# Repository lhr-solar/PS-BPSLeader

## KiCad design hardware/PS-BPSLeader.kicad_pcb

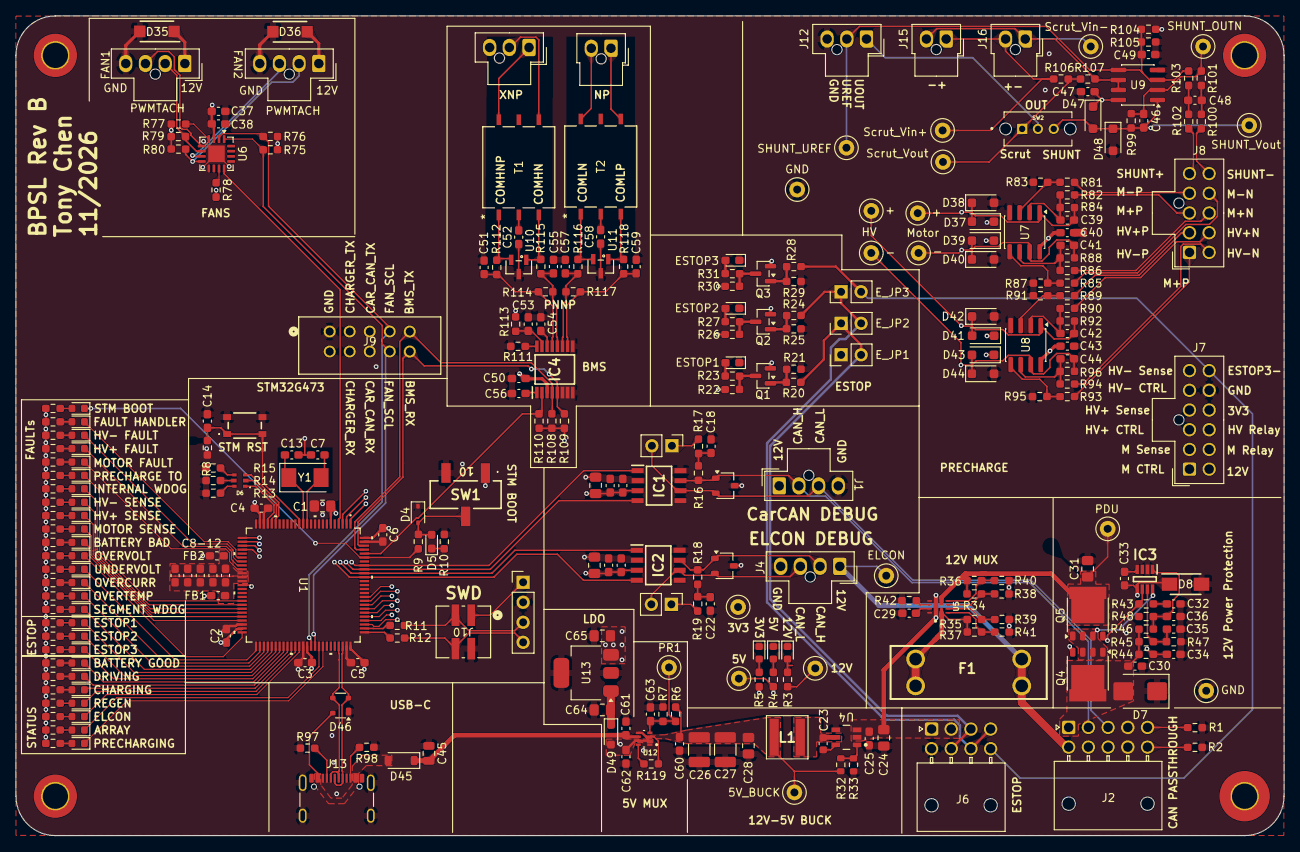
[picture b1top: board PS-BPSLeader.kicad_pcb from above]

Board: 4 copper layers, 160.9 x 104.0 mm, 315 parts (1 on the bottom side), 204 nets.

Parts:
C1, C15, C19, C31, C64, C65: 10u; C_0805_2012Metric_Pad1.18x1.45mm_HandSolder
C2, C3, C4, C5, C6, C8, C9, C12, C14, C16, C17, C18, C20, C21, C22, C30, C35, C36, C40, C43, C47, C50, C53: 0.1u; C_0603_1608Metric_Pad1.08x0.95mm_HandSolder
C7, C13: 26p; C_0603_1608Metric_Pad1.08x0.95mm_HandSolder
C10, C11, C29, C34, C37, C38: 1u; C_0603_1608Metric_Pad1.08x0.95mm_HandSolder
C23: 100n; C_0603_1608Metric
C24: 4.7u; C_0805_2012Metric_Pad1.18x1.45mm_HandSolder
C25, C48, C49: 100n; C_0603_1608Metric_Pad1.08x0.95mm_HandSolder
C26, C27: 22u; C_1210_3225Metric_Pad1.33x2.70mm_HandSolder
C28: 3.3u; C_0805_2012Metric_Pad1.18x1.45mm_HandSolder
C32: 10n; C_0603_1608Metric_Pad1.08x0.95mm_HandSolder
C33: 220n; C_0603_1608Metric_Pad1.08x0.95mm_HandSolder
C39, C41, C42, C44, C46: 1n; C_0603_1608Metric_Pad1.08x0.95mm_HandSolder
C45: 10u; C_0805_2012Metric
C51, C52, C55, C57, C58, C59: 100pF; C_0603_1608Metric_Pad1.08x0.95mm_HandSolder
C54, C56: 0.22u; C_0603_1608Metric_Pad1.08x0.95mm_HandSolder
C60, C61, C62, C63: 0.1uF; C_0603_1608Metric_Pad1.08x0.95mm_HandSolder
D1, D2, D3, D9, D10, D11, D12, D13, D14, D15, D16, D17, D18, D19, D20, D21, D22, D23, D24, D25, D26, D27, D28, D29, D30, D31, D32, D33, D34: LED; LED_0603_1608Metric
D4: TVS; D_SOD-323
D5: LED; LED_0603_1608Metric_Pad1.05x0.95mm_HandSolder
D6: RGB_LED
D7: SMBJ15CA; D_SMB
D8: SMAF4758A; SODFL5026X125N
D35, D36: VSSAF522-M3/H; SODFL5226X100N
D37, D38, D39, D40, D41, D42, D43, D44, D47, D48: TVS; D_SOD-123F
D45: D_Schottky; D_SOD-123
D46: SP0503BAHT; SOT-143
D49: SBA130CH-AU_R1_000A1; D_SOD-323_HandSoldering
E_JP1, E_JP2, E_JP3: Jumper_2_Open; PinHeader_1x02_P2.54mm_Vertical
F1: 5A; Fuse-3557-2
FAN1, FAN2: Conn_01x04; Molex_Nano-Fit_105309-xx04_1x04_P2.50mm_Vertical
FB1, FB2: FerriteBead; L_0603_1608Metric_Pad1.05x0.95mm_HandSolder
H1: MountingHole_Pad; MountingHole_3.2mm_M3_Pad_TopBottom
H2, H3, H4: MountingHole_Pad; MountingHole_3.2mm_M3_ISO14580_Pad_TopBottom
IC1, IC2: TCAN3413DR
IC3: LM74502DDFR
IC4: BQ79600PWRQ1; SOP65P640X120-16N
J1: CAR CAN DEBUG; Molex_Nano-Fit_105309-xx04_1x04_P2.50mm_Vertical
J2: LVC CAN PASSTHROUGH; Molex_Nano-Fit_105314-xx10_2x05_P2.50mm_Horizontal
J3: High Side Conn; Molex_Nano-Fit_105309-xx03_1x03_P2.50mm_Vertical
J4: ELCON CAN DEBUG; Molex_Nano-Fit_105309-xx04_1x04_P2.50mm_Vertical
J5: Low SIde Conn; Molex_Nano-Fit_105309-xx02_1x02_P2.50mm_Vertical
J6: ESTOP Connector; Molex_Nano-Fit_105314-xx08_2x04_P2.50mm_Horizontal
J7: Contactor Control; Molex_Nano-Fit_105310-xx12_2x06_P2.50mm_Vertical
J8: Voltage and Current Sense; Molex_Nano-Fit_105310-xx10_2x05_P2.50mm_Vertical
J9: LogicAnalyzer; CONN_SFH11-xxxC-D05-ST-XX_SUL
J10: SWD_Header; SWD_Conn
J11: SWD; PinHeader_1x04_P2.54mm_Vertical
J12: Shunt Breakout; Molex_Nano-Fit_105309-xx03_1x03_P2.50mm_Vertical
J13: USB_C_Receptacle_USB2.0_16P; USB_C_Receptacle_GCT_USB4105-xx-A_16P_TopMnt_Horizontal
J15: Discharge Vin; Molex_Nano-Fit_105309-xx02_1x02_P2.50mm_Vertical
J16: Charge Vin; Molex_Nano-Fit_105309-xx02_1x02_P2.50mm_Vertical
JP1, JP2: TRM; PinHeader_1x02_P2.54mm_Vertical
L1: 8.2u; XAL5050822MEC
LED1: ESTOP1; LED_0603_1608Metric_Pad1.05x0.95mm_HandSolder
LED2: ESTOP2; LED_0603_1608Metric_Pad1.05x0.95mm_HandSolder
LED3: ESTOP3; LED_0603_1608Metric_Pad1.05x0.95mm_HandSolder
LOGO1: Dr. Hallock; LHRs_LOGO
LOGO2: Dr. Hallock; Hallock_Image_Tiny
Q1, Q2, Q3: SQ2315CES-T1_GE3; SOT-23
Q4, Q5: PSMN012-100YS; LFPAK56
R1, R2: 0; R_0603_1608Metric_Pad0.98x0.95mm_HandSolder
R3: 4.3k; R_0603_1608Metric_Pad0.98x0.95mm_HandSolder
R4: 1.5k; R_0603_1608Metric_Pad0.98x0.95mm_HandSolder
R5, R10, R13, R14, R15, R23, R27, R31, R49, R50, R51, R52, R53, R54, R55, R56, R57, R58, R59, R60, R61, R62, R63, R64, R65, R66, R67, R68, R69, R70, R71, R72, R73, R74, R114, R117: 1k; R_0603_1608Metric_Pad0.98x0.95mm_HandSolder
R6, R48: 16k; R_0603_1608Metric_Pad0.98x0.95mm_HandSolder
R7: 4.7k; R_0603_1608Metric_Pad0.98x0.95mm_HandSolder
R8, R9, R21, R22, R25, R26, R29, R30, R44, R75, R76, R79, R80, R81, R82, R83, R84, R85, R86, R87, R88, R89, R90, R91, R92, R93, R94, R95, R96, R99, R101, R103, R107, R108, R109, R119: 10k; R_0603_1608Metric_Pad0.98x0.95mm_HandSolder
R11, R12: 22; R_0603_1608Metric_Pad0.98x0.95mm_HandSolder
R16, R17, R18, R19: 60; R_0603_1608Metric_Pad0.98x0.95mm_HandSolder
R20, R24, R28, R77, R78: 33k; R_0603_1608Metric_Pad0.98x0.95mm_HandSolder
R32: 100k; R_0603_1608Metric
R33: 19.1k; R_0603_1608Metric
R34: 57.6k; R_0603_1608Metric_Pad0.98x0.95mm_HandSolder
R35: 67.3k; R_0603_1608Metric_Pad0.98x0.95mm_HandSolder
R36: 26.1k; R_0603_1608Metric_Pad0.98x0.95mm_HandSolder
R37: 37.4k; R_0603_1608Metric_Pad0.98x0.95mm_HandSolder
R38, R39, R40, R41: 5k; R_0603_1608Metric_Pad0.98x0.95mm_HandSolder
R42: 22.1k; R_0603_1608Metric_Pad0.98x0.95mm_HandSolder
R43: 33; R_0603_1608Metric_Pad0.98x0.95mm_HandSolder
R45, R46, R110, R111: 100k; R_0603_1608Metric_Pad0.98x0.95mm_HandSolder
R47: 7.5k; R_0603_1608Metric_Pad0.98x0.95mm_HandSolder
R97, R98: 5.1k; R_0603_1608Metric_Pad0.98x0.95mm_HandSolder
R100, R102: 100; R_0603_1608Metric_Pad0.98x0.95mm_HandSolder
R104, R105: 20k; R_0603_1608Metric_Pad0.98x0.95mm_HandSolder
R106: 90.9k; R_0603_1608Metric_Pad0.98x0.95mm_HandSolder
R112, R115, R116, R118: 51; R_0603_1608Metric_Pad0.98x0.95mm_HandSolder
R113: 10; R_0603_1608Metric_Pad0.98x0.95mm_HandSolder
Reset1: Reset; TL3365AF180QG
SW1: SW_SPDT; BootSW
SW2: OS102011MS2QN1; SW_OS102011MS2QN1
T1, T2: HMU1228NL; HMU1228NL_PUL
TP1: PDU; TestPoint_Loop_D1.80mm_Drill1.0mm_Beaded
TP2: 12V_MUX; TestPoint_Loop_D1.80mm_Drill1.0mm_Beaded
TP3, TP4: GND; TestPoint_Loop_D1.80mm_Drill1.0mm_Beaded
TP5: ELCON; TestPoint_Loop_D1.80mm_Drill1.0mm_Beaded
TP6: 5V_BUCK; TestPoint_Loop_D1.80mm_Drill1.0mm_Beaded
TP7: 5V; TestPoint_Loop_D1.80mm_Drill1.0mm_Beaded
TP8: 5V_USB; TestPoint_Loop_D1.80mm_Drill1.0mm_Beaded
TP9: HV+; TestPoint_Loop_D1.80mm_Drill1.0mm_Beaded
TP10: Motor+; TestPoint_Loop_D1.80mm_Drill1.0mm_Beaded
TP11: HV-; TestPoint_Loop_D1.80mm_Drill1.0mm_Beaded
TP12: Motor-; TestPoint_Loop_D1.80mm_Drill1.0mm_Beaded
TP13: SHUNT_OUTN; TestPoint_Loop_D1.80mm_Drill1.0mm_Beaded
TP14: SHUNT_Vout; TestPoint_Loop_D1.80mm_Drill1.0mm_Beaded
TP15: SHUNT_UREF; TestPoint_Loop_D1.80mm_Drill1.0mm_Beaded
TP16: Scrut_Vin+; TestPoint_Loop_D1.80mm_Drill1.0mm_Beaded
TP17: Scrut_Vout; TestPoint_Loop_D1.80mm_Drill1.0mm_Beaded
TP18: Scrut_Vin-; TestPoint_Loop_D1.80mm_Drill1.0mm_Beaded
TP_3.3V1: 3.3V; TestPoint_Loop_D1.80mm_Drill1.0mm_Beaded
U1: STM32G473VETx; 100PinMCU
U2, U3: CDSOT23-T24CAN
U4: LMR51635XDDCR; DDC0006A-MFG
U5: TPS2121RUXR
U6: EMC2305-1-AP-TR; Texas_RGV0016A_VQFN-16-1EP_4x4mm_P0.65mm_EP2.1x2.1mm
U7, U8, U9: TLV9002QDRQ1; SOIC-8_3.9x4.9mm_P1.27mm
U10, U11: PESD5V0L2BT; SOT23_NXP
U12: TPS2117DRLR
U13: MCP1826S; SOT-223-3_TabPin2
Y1: Crystal; Crystal_SMD_Abracon_ABM3-2Pin_5.0x3.2mm

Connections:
+3V3: C1.1, C2.1, C3.1, C4.1, C5.1, C6.1, C15.1, C16.1, C17.1, C19.1, C20.1, C21.1, C37.1, C38.1, C40.1, C43.1, C47.1, C50.1, C65.2, D37.1 (K), D39.1 (K), D41.1 (K), D43.1 (K), D47.1 (K), FB1.1, IC1.3 (VCC), IC1.5 (SHDNV_IO), IC2.3 (VCC), IC2.5 (SHDNV_IO), IC4.3 (VIO), J7.9, J10.1, J11.1, Q1.2 (S), Q2.2 (S), Q3.2 (S), R5.1, R8.2, R49.1, R50.1, R51.1, R52.1, R53.1, R54.1, R55.1, R56.1, R57.1, R58.1, R59.1, R60.1, R61.1, R62.1, R63.1, R64.1, R65.1, R66.1, R67.1, R68.1, R69.1, R70.1, R71.1, R72.1, R73.1, R74.1, R75.1, R76.1, R77.1, R78.1, R79.1, R80.1, R104.2, R108.1, R109.1, R110.1, SW1.1 (A), TP_3.3V1.1 (1_1), U1.6 (VBAT), U1.24 (VDD), U1.49 (VDD), U1.64 (VDD), U1.75 (VDD), U1.100 (VDD), U6.3 (VDD), U7.8 (V+), U8.8 (V+), U9.8 (V+), U13.3 (VO)
+5V: C62.1, D49.2 (A), R4.1, TP7.1 (1_1), U12.2 (VOUT), U12.7 (VOUT__1)
+12V: C24.1, C25.1, D35.1 (K), D36.1 (K), E_JP1.1 (A), FAN1.1, FAN2.1, J1.1 (12V), J6.1, J6.2, J7.12, R3.1, R113.2, TP2.1 (1_1), U4.2 (EN), U4.3 (VIN), U5.1 (OUT), U5.8 (OUT)
/BMS/COMHN: C55.1, IC4.12 (COMHN), R114.2, R115.1
/BMS/COMHP: C51.1, IC4.13 (COMHP), R112.1, R114.1
/BMS/COMLN: C57.1, IC4.11 (COMLN), R116.1, R117.1
/BMS/COMLP: C59.1, IC4.10 (COMLP), R117.2, R118.1
/BMS/INH: IC4.16 (INH), R111.1
/BMS_NFAULT: IC4.2 (NFAULT), R110.2, U1.96 (PB9)
/BMS_UART_RX: IC4.5 (MISO/TX), J9.10 (CH0), R109.2, U1.98 (PE1)
/BMS_UART_TX: IC4.4 (MOSI/RX), J9.9 (CH1), R108.2, U1.97 (PE0)
/CAR_CAN_H: IC1.7 (CANH), J1.2 (CAN_H), J2.2 (CAN_H), R16.1, U2.1 (CAN_H)
/CAR_CAN_L: IC1.6 (CANL), J1.3 (CAN_L), J2.3 (CAN_L), JP1.2 (B), U2.2 (CAN_L)
/CHARGER_CAN_H: IC2.7 (CANH), J2.9 (CAN_H), J4.2 (CAN_H), R18.1, U3.1 (CAN_H)
/CHARGER_CAN_L: IC2.6 (CANL), J2.8 (CAN_L), J4.3 (CAN_L), JP2.2 (B), U3.2 (CAN_L)
/ELCON_LV+: F1.1, J2.10 (12V), J4.1 (12V), TP5.1 (1_1)
/ESTOP_1-/2+: E_JP1.2 (B), E_JP2.1 (A), J6.3, J6.7, R20.2
/ESTOP_1_SENSE: R22.2, U1.1 (PE2)
/ESTOP_2-/3+: E_JP2.2 (B), E_JP3.1 (A), J6.4, J6.6, R24.2
/ESTOP_2_SENSE: R26.2, U1.2 (PE3)
/ESTOP_3-: E_JP3.2 (B), J6.5, J7.7, R28.2
/ESTOP_3_SENSE: R30.2, U1.3 (PE4)
/FAN_ALERT: U1.4 (PE5), U6.12 (*ALERT)
/FAN_SCL: J9.7 (CH3), R76.2, U1.65 (PC6), U6.2 (SMCLK)
/FAN_SDA: J9.8 (CH2), R75.2, U1.66 (PC7), U6.1 (SMDATA)
/Fan/ADDRESS_PULLUP: R77.2, U6.4 (ADDR_SEL)
/Fan/FAN_1_PWM: FAN1.3, U6.5 (PWM1)
/Fan/FAN_1_TACH: FAN1.2, R79.2, U6.6 (TACH1)
/Fan/FAN_2_PWM: FAN2.3, U6.7 (PWM2)
/Fan/FAN_2_TACH: FAN2.2, R80.2, U6.8 (TACH2)
/HV+N: J8.9, R90.1
/HV+P: J8.2, R89.1
/HV+_CTRL: J7.3, U1.82 (PD0)
/HV+_SENSE: J7.4, U1.83 (PD1)
/HV-N: J8.10, R94.1
/HV-P: J8.1, R93.1
/HV-_CTRL: J7.5, U1.84 (PD2)
/HV-_SENSE: J7.6, U1.85 (PD3)
/HV_Relay: J7.10, U1.81 (PC12)
/MOTOR_CTRL: J7.1, U1.78 (PA15)
/MOTOR_SENSE: J7.2, U1.80 (PC11)
/Motor+N: J8.8, R86.1
/Motor+P: J8.3, R82.1
/Motor-N: J8.7, R85.1
/Motor-P: J8.4, R81.1
/Motor_Relay: J7.11, U1.79 (PC10)
/PDU_LV+: C30.1, D7.2 (A2), J2.1 (12V), Q4.5, R44.2, R45.1, R46.1
/Peripherals/100PinMCU/BOOT0: D34.1 (K), R9.1, U1.95 (PB8-BOOT0)
/Peripherals/100PinMCU/GNDA: C8.2, C9.2, C10.2, C11.2, C12.2, FB2.1, U1.35 (VSSA)
/Peripherals/100PinMCU/NRST: C14.1, R8.1, Reset1.1, U1.14 (PG10-NRST)
/Peripherals/100PinMCU/PA0: D6.5, U1.20 (PA0-GPIO_BLUE)
/Peripherals/100PinMCU/PA1: D6.3, U1.21 (PA1-GPIO_RED)
/Peripherals/100PinMCU/PA2: D6.1, U1.22 (PA2-GPIO_GREEN)
/Peripherals/100PinMCU/PB0: D32.1 (K), U1.32 (PB0)
/Peripherals/100PinMCU/PB1: D24.1 (K), U1.33 (PB1)
/Peripherals/100PinMCU/PB2: D33.1 (K), U1.34 (PB2)
/Peripherals/100PinMCU/PB10: D23.1 (K), U1.47 (PB10)
/Peripherals/100PinMCU/PB11: D11.1 (K), U1.50 (PB11)
/Peripherals/100PinMCU/PB12: D18.1 (K), U1.51 (PB12)
/Peripherals/100PinMCU/PB13: D10.1 (K), U1.52 (PB13)
/Peripherals/100PinMCU/PB14: D29.1 (K), U1.53 (PB14)
/Peripherals/100PinMCU/PB15: D13.1 (K), U1.54 (PB15)
/Peripherals/100PinMCU/PC5: D9.1 (K), U1.31 (PC5)
/Peripherals/100PinMCU/PC8: D19.1 (K), U1.67 (PC8)
/Peripherals/100PinMCU/PC9: D17.1 (K), U1.68 (PC9)
/Peripherals/100PinMCU/PD8: D14.1 (K), U1.55 (PD8)
/Peripherals/100PinMCU/PD9: D21.1 (K), U1.56 (PD9)
/Peripherals/100PinMCU/PD10: D28.1 (K), U1.57 (PD10)
/Peripherals/100PinMCU/PD11: D22.1 (K), U1.58 (PD11)
/Peripherals/100PinMCU/PD12: D16.1 (K), U1.59 (PD12)
/Peripherals/100PinMCU/PD13: D15.1 (K), U1.60 (PD13)
/Peripherals/100PinMCU/PD14: D25.1 (K), U1.61 (PD14)
/Peripherals/100PinMCU/PD15: D12.1 (K), U1.62 (PD15)
/Peripherals/100PinMCU/PE11: D26.1 (K), U1.42 (PE11)
/Peripherals/100PinMCU/PE12: D30.1 (K), U1.43 (PE12)
/Peripherals/100PinMCU/PE13: D27.1 (K), U1.44 (PE13)
/Peripherals/100PinMCU/PE14: D20.1 (K), U1.45 (PE14)
/Peripherals/100PinMCU/PE15: D31.1 (K), U1.46 (PE15)
/Peripherals/100PinMCU/SWCLK: R11.1, U1.77 (PA14)
/Peripherals/100PinMCU/SWDIO: R12.1, U1.76 (PA13)
/Peripherals/100PinMCU/VDDA: C8.1, C9.1, C10.1, C11.1, C12.1, FB1.2, U1.36 (VREF+), U1.37 (VDDA)
/Peripherals/CAR_CAN_RX: IC1.4 (RXD), J9.6 (CH4), U1.92 (PB5)
/Peripherals/CAR_CAN_TX: IC1.1 (TXD), J9.5 (CH5), U1.93 (PB6)
/Peripherals/CHARGER_CAN_RX: IC2.4 (RXD), J9.4 (CH6), U1.90 (PB3)
/Peripherals/CHARGER_CAN_TX: IC2.1 (TXD), J9.3 (CH7), U1.91 (PB4)
/Peripherals/HV+: C42.2, D41.2 (A), D42.1 (K), R92.1, TP9.1 (1_1), U1.28 (PA6), U8.1
/Peripherals/HV-: C44.2, D43.2 (A), D44.1 (K), R96.1, TP11.1 (1_1), U1.29 (PA7), U8.7
/Peripherals/High Voltage Peripherals/Current_Sense/SHUNT Vout: C46.1, D47.2 (A), D48.1 (K), R99.1, SW2.3 (C), TP14.1 (1_1), U9.1
/Peripherals/High Voltage Peripherals/Current_Sense/Scrut Vout: R106.2, R107.1, SW2.1 (A), TP17.1 (1_1)
/Peripherals/High Voltage Peripherals/Current_Sense/Vin+: J15.1, J16.2, R106.1, TP16.1 (1_1)
/Peripherals/High Voltage Peripherals/Current_Sense/Vin-: J15.2, J16.1, R107.2, TP18.1 (1_1), U9.6 (-), U9.7
/Peripherals/High Voltage Peripherals/SHUNT_UOUT: J12.1, SW2.2 (B)
/Peripherals/High Voltage Peripherals/SHUNT_UREF: C49.1, J12.2, R103.1, R104.1, R105.1, TP15.1 (1_1), U9.3 (+), U9.5 (+)
/Peripherals/Motor+: C39.2, D37.2 (A), D38.1 (K), R84.1, TP10.1 (1_1), U1.26 (PA4), U7.1
/Peripherals/Motor-: C41.2, D39.2 (A), D40.1 (K), R88.1, TP12.1 (1_1), U1.27 (PA5), U7.7
/Power/5V_BUCK: C26.1, C27.1, C28.1, C60.1, L1.2, R6.1, R32.1, R119.1, TP6.1 (1_1), U12.3 (VIN1), U12.5 (MODE)
/Power/12VBuck/CB: C23.1, U4.6 (CB)
/Power/12VBuck/FB: R32.2, R33.1, U4.1 (FB)
/Power/12VBuck/SW: C23.2, L1.1, U4.5 (SW)
/Power/PDU_12V: C31.1, Q5.5, R34.1, R36.1, TP1.1 (1_1), U5.7 (IN1)
/Power/PowerProtection/EN/UVLO: C36.1, IC3.1 (EN/UVLO), R46.2, R48.2
/Power/PowerProtection/OV: C35.1, IC3.7 (OV), R45.2, R47.1
/Power/PowerProtection/gate: IC3.6 (GATE), Q4.4, Q5.4, R43.2
/Power/PowerProtection/source: IC3.8 (SRC), Q4.1, Q4.2, Q4.3, Q5.1, Q5.2, Q5.3
/Power/Power_5VMux/PR1: C63.1, R6.2, R7.1, TP8.1 (1_1), U12.4 (PR1)
/Power/Power_Mux_PDU_ELCON/CP2: R37.2, R41.1, U5.3 (CP2)
/Power/Power_Mux_PDU_ELCON/OV1: R34.2, R38.1, U5.5 (OV1)
/Power/Power_Mux_PDU_ELCON/OV2: R35.2, R39.1, U5.4 (OV2)
/Power/Power_Mux_PDU_ELCON/PRI: R36.2, R40.1, U5.6 (PR1)
/Power/Power_Mux_PDU_ELCON/Vin2: F1.2, R35.1, R37.1, U5.2 (IN2)
/SHUNT+: J8.5, R102.2
/SHUNT-: J8.6, R100.2
/USB-C_Connector/CC1: J13.A5 (CC1), R97.2
/USB-C_Connector/CC2: J13.B5 (CC2), R98.2
/USB-C_Connector/VBUS_IN: D45.2 (A), D46.4 (K), J13.A4 (VBUS), J13.A9 (VBUS), J13.B4 (VBUS), J13.B9 (VBUS)
/USB_D+: D46.2 (K), J13.A6 (D+), J13.B6 (D+), U1.73 (PA12)
/USB_D-: D46.3 (K), J13.A7 (D-), J13.B7 (D-), U1.72 (PA11)
/USB_VBUS_IN: C45.2, C61.1, D45.1 (K), U12.6 (VIN2)
/isolatedCOMHN: J3.2, T1.4 (TX-)
/isolatedCOMHP: J3.1, T1.6 (TX+)
/isolatedCOMLN: J5.2, T2.6 (TX+)
/isolatedCOMLP: J5.1, T2.4 (TX-)
GND: C1.2, C2.2, C3.2, C4.2, C5.2, C6.2, C7.1, C13.1, C14.2, C15.2, C16.2, C17.2, C18.2, C19.2, C20.2, C21.2, C22.2, C24.2, C25.2, C26.2, C27.2, C28.2, C29.2, C30.2, C31.2, C32.2, C34.1, C35.2, C36.2, C37.2, C38.2, C40.2, C43.2, C45.1, C47.2, C49.2, C50.2, C51.2, C52.1, C53.2, C54.2, C55.2, C56.2, C57.2, C58.1, C59.2, C60.2, C61.2, C62.2, C63.2, C64.1, C65.1, D1.1 (K), D2.1 (K), D3.1 (K), D4.1 (A1), D7.1 (A1), D8.2 (A), D35.2 (A), D36.2 (A), D38.2 (A), D40.2 (A), D42.2 (A), D44.2 (A), D46.1 (A), D48.2 (A), FAN1.4, FAN2.4, FB2.2, IC1.2 (GND), IC1.8 (STB), IC2.2 (GND), IC2.8 (STB), IC3.2 (GND), IC4.6 (SCLK), IC4.7 (NCS), IC4.8 (NUART/SPI_(SPI_RDY)), IC4.9 (GND), J1.4 (GND), J2.4 (GND), J2.7 (GND), J4.4 (GND), J6.8, J7.8, J9.1 (GND), J10.2, J11.2, J12.3, J13.A1 (GND), J13.A12 (GND), J13.B1 (GND), J13.B12 (GND), J13.S1 (SHIELD), J13.S2 (Shield), J13.S3 (Shield), J13.S4 (Shield), LED1.1 (K), LED2.1 (K), LED3.1 (K), R1.2, R2.2, R7.2, R10.2, R13.2, R14.2, R15.2, R21.1, R25.1, R29.1, R33.2, R38.2, R39.2, R40.2, R41.2, R42.2, R47.2, R48.1, R83.1, R87.1, R91.1, R95.1, R97.1, R98.1, R105.2, R111.2, Reset1.2, SW1.3 (C), TP3.1 (1_1), TP4.1 (1_1), U1.23 (VSS), U1.48 (VSS), U1.63 (VSS), U1.74 (VSS), U1.99 (VSS), U2.3 (GND), U3.3 (GND), U4.4 (GND), U5.9 (ST), U5.12 (GND), U6.17 (EPAD), U7.4 (V-), U8.4 (V-), U9.4 (V-), U10.3, U11.3, U12.1 (GND), U13.2 (GND)
unnamed: C18.1, R16.2, R17.1
unnamed: C22.1, R18.2, R19.1
unnamed: C32.1, R43.1
unnamed: C48.1, R100.1, R101.2
unnamed: C48.2, R102.1, R103.2
unnamed: D1.2 (A), R3.2
unnamed: D2.2 (A), R4.2
unnamed: D3.2 (A), R5.2
unnamed: D4.2 (A2), D5.2 (A), R9.2, SW1.2 (B)
unnamed: D5.1 (K), R10.1
unnamed: D6.2, R13.1
unnamed: D6.4, R14.1
unnamed: D6.6, R15.1
unnamed: C33.1, C34.2, D8.1 (K), IC3.5 (VS), R44.1
unnamed: D9.2 (A), R49.2
unnamed: D10.2 (A), R50.2
unnamed: D11.2 (A), R51.2
unnamed: D12.2 (A), R52.2
unnamed: D13.2 (A), R53.2
unnamed: D14.2 (A), R54.2
unnamed: D15.2 (A), R55.2
unnamed: D16.2 (A), R56.2
unnamed: D17.2 (A), R57.2
unnamed: D18.2 (A), R58.2
unnamed: D19.2 (A), R59.2
unnamed: D20.2 (A), R60.2
unnamed: D21.2 (A), R61.2
unnamed: D22.2 (A), R62.2
unnamed: D23.2 (A), R63.2
unnamed: D24.2 (A), R64.2
unnamed: D25.2 (A), R65.2
unnamed: D26.2 (A), R66.2
unnamed: D27.2 (A), R67.2
unnamed: D28.2 (A), R68.2
unnamed: D29.2 (A), R69.2
unnamed: D30.2 (A), R70.2
unnamed: D31.2 (A), R71.2
unnamed: D32.2 (A), R72.2
unnamed: D33.2 (A), R73.2
unnamed: D34.2 (A), R74.2
unnamed: C64.2, D49.1 (K), U13.1 (VI)
unnamed: C33.2, IC3.4 (VCAP)
unnamed: C53.1, IC4.15 (BAT), R113.1
unnamed: C54.1, IC4.14 (CVDD)
unnamed: C56.1, IC4.1 (DVDD)
unnamed: J2.5 (SHIELD), R1.1
unnamed: J2.6 (SHIELD), R2.1
unnamed: J10.3, J11.3, R11.2
unnamed: J10.4, J11.4, R12.2
unnamed: JP1.1 (A), R17.2
unnamed: JP2.1 (A), R19.2
unnamed: LED1.2 (A), R23.2
unnamed: LED2.2 (A), R27.2
unnamed: LED3.2 (A), R31.2
unnamed: Q1.3 (D), R22.1, R23.1
unnamed: Q1.1 (G), R20.1, R21.2
unnamed: Q2.3 (D), R26.1, R27.1
unnamed: Q2.1 (G), R24.1, R25.2
unnamed: Q3.3 (D), R30.1, R31.1
unnamed: Q3.1 (G), R28.1, R29.2
unnamed: C52.2, T1.2 (TCT)
unnamed: R112.2, T1.1 (TD+), U10.2
unnamed: R115.2, T1.3 (TD-), U10.1
unnamed: C58.2, T2.2 (TCT)
unnamed: R116.2, T2.1 (TD+), U11.2
unnamed: R118.2, T2.3 (TD-), U11.1
unnamed: C7.2, U1.12 (PF0-OSC_IN), Y1.2
unnamed: C13.2, U1.13 (PF1-OSC_OUT), Y1.1
unnamed: R42.1, U5.10 (ILIM)
unnamed: C29.1, U5.11 (SS)
unnamed: R78.2, U6.11 (CLK)
unnamed: R81.2, R83.2, U7.3 (+)
unnamed: C39.1, R82.2, R84.2, U7.2 (-)
unnamed: R85.2, R87.2, U7.5 (+)
unnamed: C41.1, R86.2, R88.2, U7.6 (-)
unnamed: R89.2, R91.2, U8.3 (+)
unnamed: C42.1, R90.2, R92.2, U8.2 (-)
unnamed: R93.2, R95.2, U8.5 (+)
unnamed: C44.1, R94.2, R96.2, U8.6 (-)
unnamed: C46.2, R99.2, R101.1, TP13.1 (1_1), U9.2 (-)
unnamed: R119.2, U12.8 (ST)

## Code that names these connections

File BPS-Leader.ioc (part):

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Mcu.Name=STM32G473V(B-C-E)Tx
Mcu.Package=LQFP100
Mcu.UserName=STM32G473VETx
PA0.Signal=GPIO_Output
PA1.Signal=GPIO_Output
PA11.Mode=Device
PA11.Signal=USB_DM
PA12.Mode=Device
PA12.Signal=USB_DP
PA13.Mode=Serial_Wire
PA13.Signal=SYS_JTMS-SWDIO
PA14.Mode=Serial_Wire
PA14.Signal=SYS_JTCK-SWCLK
PA2.Signal=GPIO_Output
PA3.Signal=GPIO_Input
PA4.Mode=IN17-Single-Ended
PA4.Signal=ADC2_IN17
PA5.Mode=IN13-Single-Ended
PA5.Signal=ADC2_IN13
PA6.Signal=SharedAnalog_PA6
PA7.Mode=IN4-Single-Ended
PA7.Signal=ADC2_IN4
PA8.Signal=GPIO_Output
PB10.Signal=GPIO_Output
PB11.Signal=GPIO_Output
PB12.Signal=GPIO_Output
PB13.Signal=GPIO_Output
PB14.Signal=GPIO_Output
PB15.Signal=GPIO_Output
PB3.Mode=FDCAN_Activate
PB3.Signal=FDCAN3_RX
PB4.Mode=FDCAN_Activate
PB4.Signal=FDCAN3_TX
PB5.Mode=FDCAN_Activate
PB5.Signal=FDCAN2_RX
PB6.Mode=FDCAN_Activate
PB6.Signal=FDCAN2_TX
PB7.Signal=GPIO_Input
PB8-BOOT0.Signal=EVENTOUT
PB9.Signal=GPIO_Input
PC0.Signal=GPIO_Input
PC10.Mode=Asynchronous
PC10.Signal=USART3_TX
PC11.Mode=Asynchronous
PC11.Signal=USART3_RX
PC2.Signal=GPIO_Output
PC6.Mode=I2C
PC6.Signal=I2C4_SCL
PC7.Mode=I2C
PC7.Signal=I2C4_SDA
PC8.Signal=GPIO_Output
PC9.Signal=GPIO_Output
PD10.Signal=GPIO_Output
PD11.Signal=GPIO_Output
PD12.Signal=GPIO_Output
PD13.Signal=GPIO_Output
PD14.Signal=GPIO_Output
PD15.Signal=GPIO_Output
PD2.Signal=GPIO_Input
PD3.Signal=GPIO_Input
PD4.Signal=GPIO_Input
PD6.Signal=GPIO_Output
PD7.Signal=GPIO_Output
PD8.Signal=GPIO_Output
PD9.Signal=GPIO_Output
PE0.Signal=GPIO_Input
PE1.Signal=GPIO_Output
PE10.Signal=GPIO_Output
PE11.Signal=GPIO_Output
PE12.Signal=GPIO_Output
PE13.Signal=GPIO_Output
PE14.Signal=GPIO_Output
PE15.Signal=GPIO_Output
PE2.Signal=GPIO_Output
PE3.Signal=GPIO_Output
PE4.Signal=GPIO_Input
PE5.Signal=GPIO_Input
PE6.Signal=GPIO_Input
PE7.Signal=GPIO_Output
PE8.Signal=GPIO_Output
PE9.Signal=GPIO_Output
PF0-OSC_IN.Mode=HSE-External-Oscillator
PF0-OSC_IN.Signal=RCC_OSC_IN
PF1-OSC_OUT.Mode=HSE-External-Oscillator
PF1-OSC_OUT.Signal=RCC_OSC_OUT
RCC.HSE_VALUE=8000000
RCC.SYSCLKFreq_VALUE=16000000
board=custom
